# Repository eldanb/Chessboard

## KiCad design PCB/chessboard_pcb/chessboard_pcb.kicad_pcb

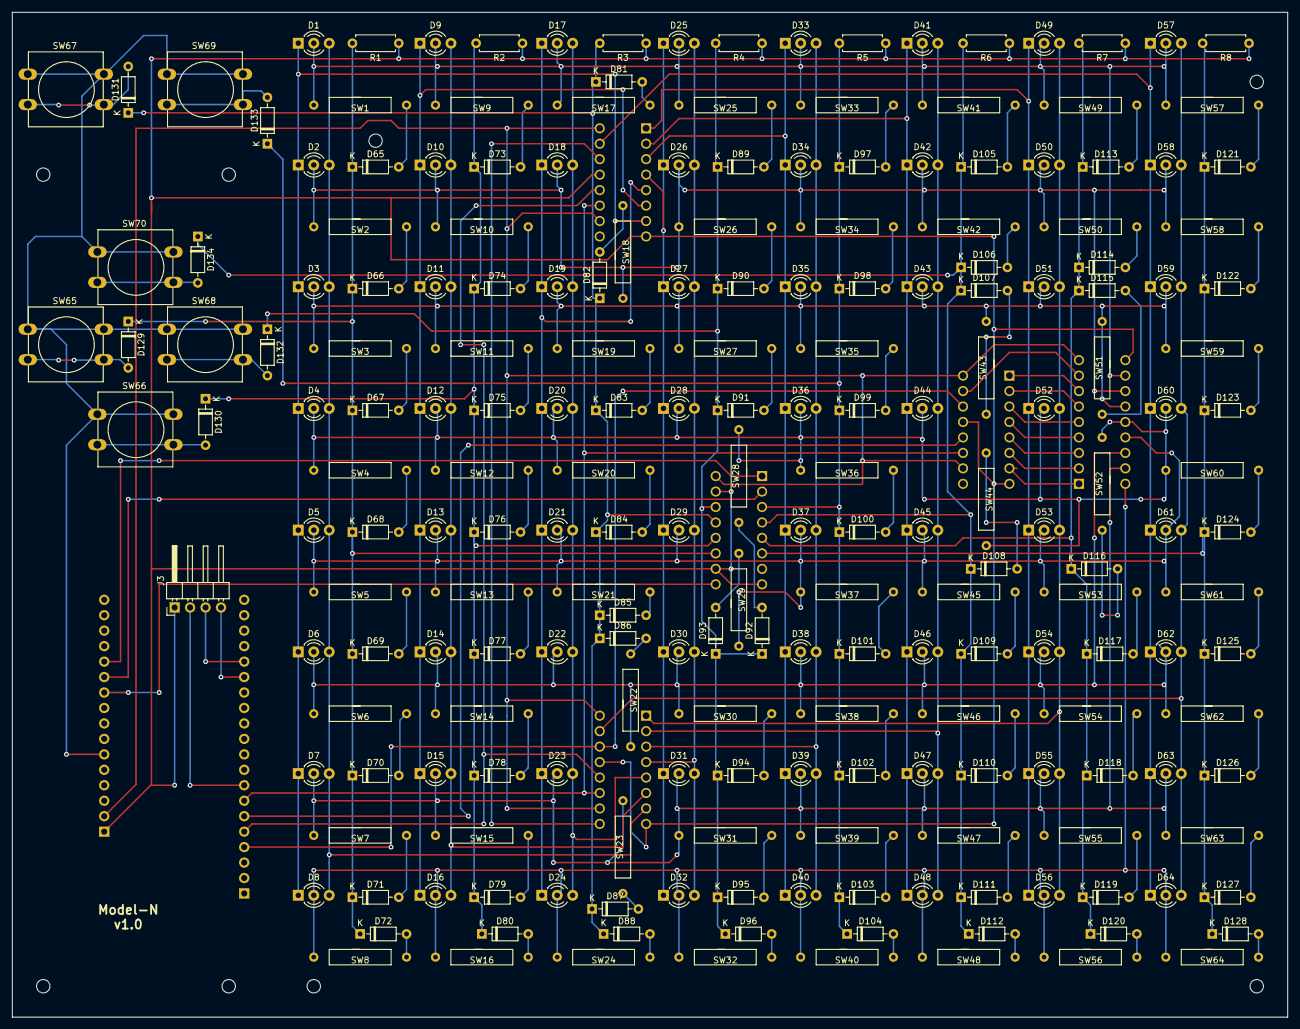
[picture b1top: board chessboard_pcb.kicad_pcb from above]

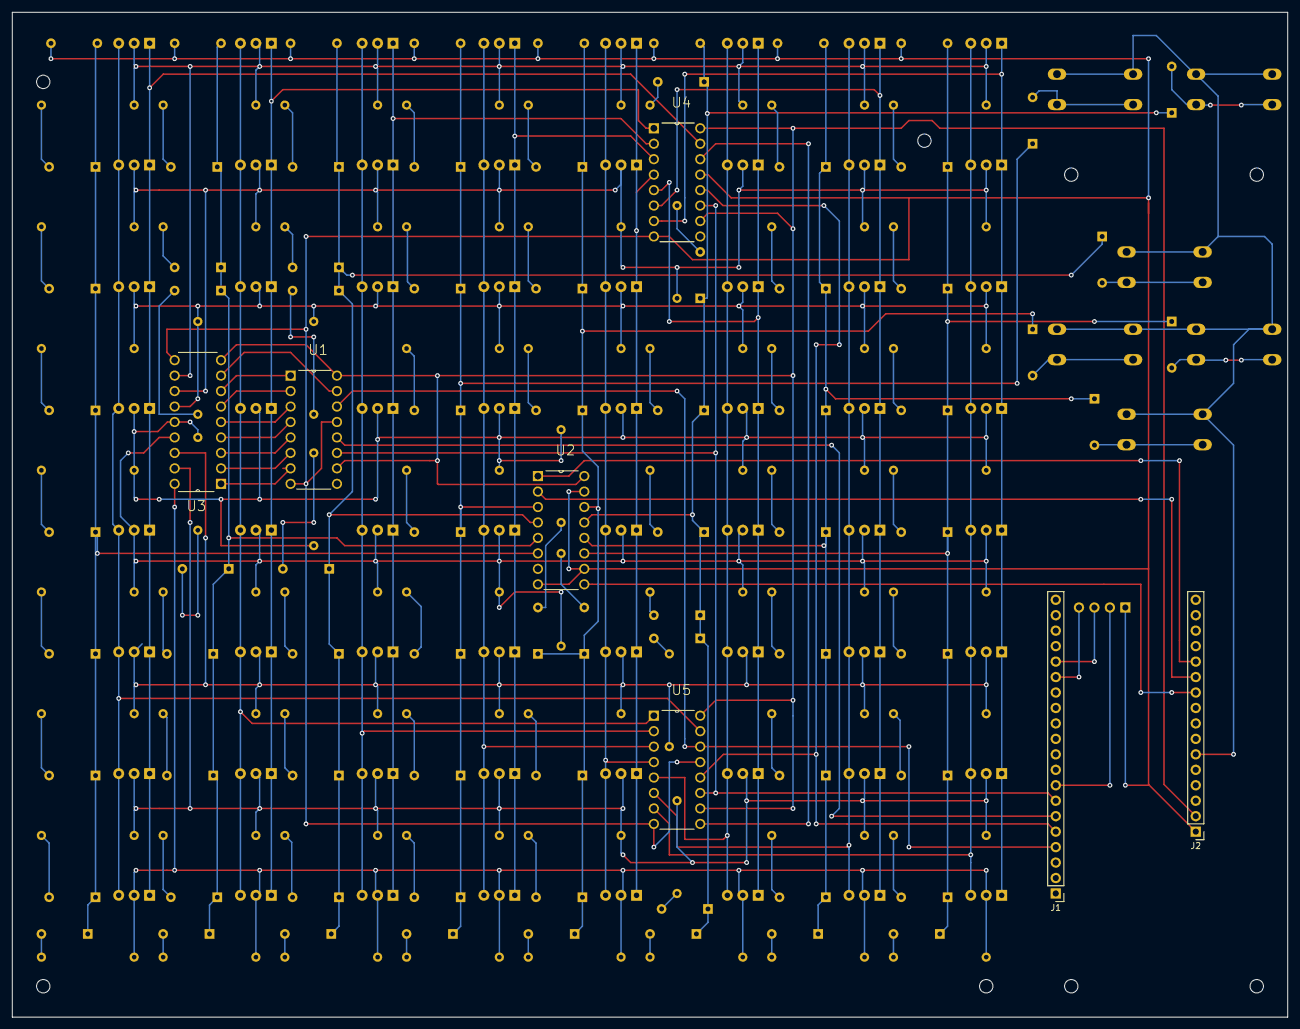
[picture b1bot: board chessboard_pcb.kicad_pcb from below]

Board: 2 copper layers, 209.6 x 165.1 mm, 220 parts (7 on the bottom side), 124 nets.

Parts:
D1, D2, D3, D4, D5, D6, D7, D8, D9, D10, D11, D12, D13, D14, D15, D16, D17, D18, D19, D20, D21, D22, D23, D24, D25, D26, D27, D28, D29, D30, D31, D32, D33, D34, D35, D36, D37, D38, D39, D40, D41, D42, D43, D44, D45, D46, D47, D48, D49, D50, D51, D52, D53, D54, D55, D56, D57, D58, D59, D60, D61, D62, D63, D64: LED_Dual_CAC; LED_D3.0mm-3
D65, D66, D67, D68, D69, D70, D71, D72, D73, D74, D75, D76, D77, D78, D79, D80, D81, D82, D83, D84, D85, D86, D87, D88, D89, D90, D91, D92, D93, D94, D95, D96, D97, D98, D99, D100, D101, D102, D103, D104, D105, D106, D107, D108, D109, D110, D111, D112, D113, D114, D115, D116, D117, D118, D119, D120, D121, D122, D123, D124, D125, D126, D127, D128, D129, D130, D131, D132, D133, D134: 1N4148; D_DO-35_SOD27_P7.62mm_Horizontal
J1: LOLIN1; PinHeader_1x20_P2.54mm_Vertical
J2: LOLIN2; PinHeader_1x16_P2.54mm_Vertical
J3: OLED; PinHeader_1x04_P2.54mm_Horizontal
R1, R2, R3, R4, R5, R6, R7, R8: 10K; R_Axial_DIN0207_L6.3mm_D2.5mm_P7.62mm_Horizontal
SW1, SW2, SW3, SW4, SW5, SW6, SW7, SW8, SW9, SW10, SW11, SW12, SW13, SW14, SW15, SW16, SW17, SW18, SW19, SW20, SW21, SW22, SW23, SW24, SW25, SW26, SW27, SW28, SW29, SW30, SW31, SW32, SW33, SW34, SW35, SW36, SW37, SW38, SW39, SW40, SW41, SW42, SW43, SW44, SW45, SW46, SW47, SW48, SW49, SW50, SW51, SW52, SW53, SW54, SW55, SW56, SW57, SW58, SW59, SW60, SW61, SW62, SW63, SW64: SW_Reed; ReedSw16mm
SW65, SW66, SW67, SW68, SW69, SW70: SW_Push_Dual; SW_PUSH-12mm
U1, U4, U5: 74HC595; DIP254P762X420-16
U2: 74HC165N; DIP254P762X420-16
U3: UDN2981; DIP254P762X533-18

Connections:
3V3: J1.8, J3.2
/LedMatrix/LedGC0: D1.1, D2.1, D3.1, D4.1, D5.1, D6.1, D7.1, D8.1, U4.7
/LedMatrix/LedGC1: D9.1, D10.1, D11.1, D12.1, D13.1, D14.1, D15.1, D16.1, U4.6
/LedMatrix/LedGC2: D17.1, D18.1, D19.1, D20.1, D21.1, D22.1, D23.1, D24.1, U4.5
/LedMatrix/LedGC3: D25.1, D26.1, D27.1, D28.1, D29.1, D30.1, D31.1, D32.1, U4.4
/LedMatrix/LedGC4: D33.1, D34.1, D35.1, D36.1, D37.1, D38.1, D39.1, D40.1, U4.3
/LedMatrix/LedGC5: D41.1, D42.1, D43.1, D44.1, D45.1, D46.1, D47.1, D48.1, U4.2
/LedMatrix/LedGC6: D49.1, D50.1, D51.1, D52.1, D53.1, D54.1, D55.1, D56.1, U4.1
/LedMatrix/LedGC7: D57.1, D58.1, D59.1, D60.1, D61.1, D62.1, D63.1, D64.1, U4.15
/LedMatrix/LedR0: D1.2, D9.2, D17.2, D25.2, D33.2, D41.2, D49.2, D57.2, SW1.1, SW9.1, SW17.1, SW25.1, SW33.1, SW41.1, SW49.1, SW57.1, U3.11
/LedMatrix/LedR1: D2.2, D10.2, D18.2, D26.2, D34.2, D42.2, D50.2, D58.2, SW2.1, SW10.1, SW18.1, SW26.1, SW34.1, SW42.1, SW50.1, SW58.1, U3.12
/LedMatrix/LedR2: D3.2, D11.2, D19.2, D27.2, D35.2, D43.2, D51.2, D59.2, SW3.1, SW11.1, SW19.1, SW27.1, SW35.1, SW43.1, SW51.1, SW59.1, U3.13
/LedMatrix/LedR3: D4.2, D12.2, D20.2, D28.2, D36.2, D44.2, D52.2, D60.2, SW4.1, SW12.1, SW20.1, SW28.1, SW36.1, SW44.1, SW52.1, SW60.1, U3.14
/LedMatrix/LedR4: D5.2, D13.2, D21.2, D29.2, D37.2, D45.2, D53.2, D61.2, SW5.1, SW13.1, SW21.1, SW29.1, SW37.1, SW45.1, SW53.1, SW61.1, U3.15
/LedMatrix/LedR5: D6.2, D14.2, D22.2, D30.2, D38.2, D46.2, D54.2, D62.2, SW6.1, SW14.1, SW22.1, SW30.1, SW38.1, SW46.1, SW54.1, SW62.1, U3.16
/LedMatrix/LedR6: D7.2, D15.2, D23.2, D31.2, D39.2, D47.2, D55.2, D63.2, SW7.1, SW15.1, SW23.1, SW31.1, SW39.1, SW47.1, SW55.1, SW63.1, U3.17
/LedMatrix/LedR7: D8.2, D16.2, D24.2, D32.2, D40.2, D48.2, D56.2, D64.2, SW8.1, SW16.1, SW24.1, SW32.1, SW40.1, SW48.1, SW56.1, SW64.1, U3.18
/LedMatrix/LedRC0: D1.3, D2.3, D3.3, D4.3, D5.3, D6.3, D7.3, D8.3, U5.7
/LedMatrix/LedRC1: D9.3, D10.3, D11.3, D12.3, D13.3, D14.3, D15.3, D16.3, U5.6
/LedMatrix/LedRC2: D17.3, D18.3, D19.3, D20.3, D21.3, D22.3, D23.3, D24.3, U5.5
/LedMatrix/LedRC3: D25.3, D26.3, D27.3, D28.3, D29.3, D30.3, D31.3, D32.3, U5.4
/LedMatrix/LedRC4: D33.3, D34.3, D35.3, D36.3, D37.3, D38.3, D39.3, D40.3, U5.3
/LedMatrix/LedRC5: D41.3, D42.3, D43.3, D44.3, D45.3, D46.3, D47.3, D48.3, U5.2
/LedMatrix/LedRC6: D49.3, D50.3, D51.3, D52.3, D53.3, D54.3, D55.3, D56.3, U5.1
/LedMatrix/LedRC7: D57.3, D58.3, D59.3, D60.3, D61.3, D62.3, D63.3, D64.3, U5.15
/SwitchMatrix/SwC0: D65.1, D66.1, D67.1, D68.1, D69.1, D70.1, D71.1, D72.1, D129.1, R1.2, U2.11
/SwitchMatrix/SwC1: D73.1, D74.1, D75.1, D76.1, D77.1, D78.1, D79.1, D80.1, D130.1, R2.2, U2.12
/SwitchMatrix/SwC2: D81.1, D82.1, D83.1, D84.1, D85.1, D86.1, D87.1, D88.1, D131.1, R3.2, U2.13
/SwitchMatrix/SwC3: D89.1, D90.1, D91.1, D92.1, D93.1, D94.1, D95.1, D96.1, D132.1, R4.2, U2.14
/SwitchMatrix/SwC4: D97.1, D98.1, D99.1, D100.1, D101.1, D102.1, D103.1, D104.1, D133.1, R5.2, U2.3
/SwitchMatrix/SwC5: D105.1, D106.1, D107.1, D108.1, D109.1, D110.1, D111.1, D112.1, D134.1, R6.2, U2.4
/SwitchMatrix/SwC6: D113.1, D114.1, D115.1, D116.1, D117.1, D118.1, D119.1, D120.1, R7.2, U2.5
/SwitchMatrix/SwC7: D121.1, D122.1, D123.1, D124.1, D125.1, D126.1, D127.1, D128.1, R8.2, U2.6
GND: J2.1, J3.1, R1.1, R2.1, R3.1, R4.1, R5.1, R6.1, R7.1, R8.1, U1.8, U1.13, U2.8, U2.10, U2.15, U3.10, U4.8, U4.13, U5.8, U5.13
LCLK: J1.5, U4.12, U5.12
unnamed: D65.2, SW1.2
unnamed: D66.2, SW2.2
unnamed: D67.2, SW3.2
unnamed: D68.2, SW4.2
unnamed: D69.2, SW5.2
unnamed: D70.2, SW6.2
unnamed: D71.2, SW7.2
unnamed: D72.2, SW8.2
unnamed: D73.2, SW9.2
unnamed: D74.2, SW10.2
unnamed: D75.2, SW11.2
unnamed: D76.2, SW12.2
unnamed: D77.2, SW13.2
unnamed: D78.2, SW14.2
unnamed: D79.2, SW15.2
unnamed: D80.2, SW16.2
unnamed: D81.2, SW17.2
unnamed: D82.2, SW18.2
unnamed: D83.2, SW19.2
unnamed: D84.2, SW20.2
unnamed: D85.2, SW21.2
unnamed: D86.2, SW22.2
unnamed: D87.2, SW23.2
unnamed: D88.2, SW24.2
unnamed: D89.2, SW25.2
unnamed: D90.2, SW26.2
unnamed: D91.2, SW27.2
unnamed: D92.2, SW28.2
unnamed: D93.2, SW29.2
unnamed: D94.2, SW30.2
unnamed: D95.2, SW31.2
unnamed: D96.2, SW32.2
unnamed: D97.2, SW33.2
unnamed: D98.2, SW34.2
unnamed: D99.2, SW35.2
unnamed: D100.2, SW36.2
unnamed: D101.2, SW37.2
unnamed: D102.2, SW38.2
unnamed: D103.2, SW39.2
unnamed: D104.2, SW40.2
unnamed: D105.2, SW41.2
unnamed: D106.2, SW42.2
unnamed: D107.2, SW43.2
unnamed: D108.2, SW44.2
unnamed: D109.2, SW45.2
unnamed: D110.2, SW46.2
unnamed: D111.2, SW47.2
unnamed: D112.2, SW48.2
unnamed: D113.2, SW49.2
unnamed: D114.2, SW50.2
unnamed: D115.2, SW51.2
unnamed: D116.2, SW52.2
unnamed: D117.2, SW53.2
unnamed: D118.2, SW54.2
unnamed: D119.2, SW55.2
unnamed: D120.2, SW56.2
unnamed: D121.2, SW57.2
unnamed: D122.2, SW58.2
unnamed: D123.2, SW59.2
unnamed: D124.2, SW60.2
unnamed: D125.2, SW61.2
unnamed: D126.2, SW62.2
unnamed: D127.2, SW63.2
unnamed: D128.2, SW64.2
unnamed: D129.2, SW65.2
unnamed: D130.2, SW66.2
unnamed: D131.2, SW67.2
unnamed: D132.2, SW68.2
unnamed: D133.2, SW69.2
unnamed: D134.2, SW70.2
unnamed: U1.1, U3.7
unnamed: U1.2, U3.6
unnamed: U1.3, U3.5
unnamed: U1.4, U3.4
unnamed: U1.5, U3.3
unnamed: U1.6, U3.2
unnamed: U1.7, U3.1
unnamed: U1.15, U3.8
unnamed: U4.14, U5.9
RCLK: J1.6, U1.12
RLDS: J1.4, U1.14, U5.14
SCL: J1.16, J3.3
SDA: J1.15, J3.4
SHCLK: J1.7, U1.11, U4.11, U5.11
SWCLK: J2.11, U2.2
SWDAT: J2.10, U2.9
SWRCP: J2.6, SW65.1, SW66.1, SW67.1, SW68.1, SW69.1, SW70.1
SWSL: J2.12, U2.1
VCC: J2.2, U1.10, U1.16, U2.16, U3.9, U4.10, U4.16, U5.10, U5.16

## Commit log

2021-12-29 Initial working version commit
